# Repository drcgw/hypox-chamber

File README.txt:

Initial Raspberry Pi 4 set up

Using the Raspberry Pi OS installer (https://www.raspberrypi.com/software/) and a blank microSD card (128 GB Recommended) write the raspbian OS onto the SD card. Under the "operating system" menu select "Raspberry Pi OS (other)" and select "Raspberry Pi OS Full (32-bit)". Once the operating system is written to the SD card placed into Raspberry Pi. 

Once initial setup is completed go to terminal (Ctrl + T) and run the following codes:
    sudo apt update
    sudo apt full-upgrade

Next step is to download WiringPi:
    sudo apt-get update
    git clone https://github.com/WiringPi/WiringPi
    cd WiringPi
    ./build

Once these applications have been downloaded check the version by running:
    gpio -v
    gpio readall

System settings also need to be modified. Go to the configuration settings by using the following code: 
    sudo raspi-config
    
Under "Interfacing Options" insure that camera, SSH, VNC, SPI, I2C, Serial, and Remote GPIO are all enabled
System will require a reboot following these changes. The final items that need to be installed are all the python packaged and adafruit system requirements for CircuitPython. Tutorials and information can be found on Adafruit's website (https://learn.adafruit.com/welcome-to-circuitpython).
    sudo pip3 install adafruit-circuitpython-ads1x15
    sudo pip3 install adafruit-circuitpython-bme280
    sudo pip3 install adafruit-circuitpython-mcp9808
    sudo pip3 install adafruit-circuitpython-ccs811
    sudo pip3 install adafruit-circuitpython-bh1750

Once all the background files have been downloaded the github library can be downloaded using 
    wget https://github.com/drcgw/hypox-chamber.git

Unpack the files by unzipping and move RunChamber.sh file to the desktop.

Files can also be run manually through the terminal. Move the "PythonScript/" folder under "Documents/". If running manually before each run create a folder under "Documents/" with the following naming format "YYYY-MM-DD-Exposure/". Once inside this directory create: "FinalData/", "RawData/", "Calibration/" & "ImageCapture/" folders. After these folders have been created the exposure code can be run using the follow codes in the terminal. 
	cd Documents/PythonCodes/
	python3 2022-02-15-HC2000.py

If running it manually make sure that the most recent code has been installed and change the name in the second line of the above code to match the most recent copy of the .py script under the PythonCodes folder.

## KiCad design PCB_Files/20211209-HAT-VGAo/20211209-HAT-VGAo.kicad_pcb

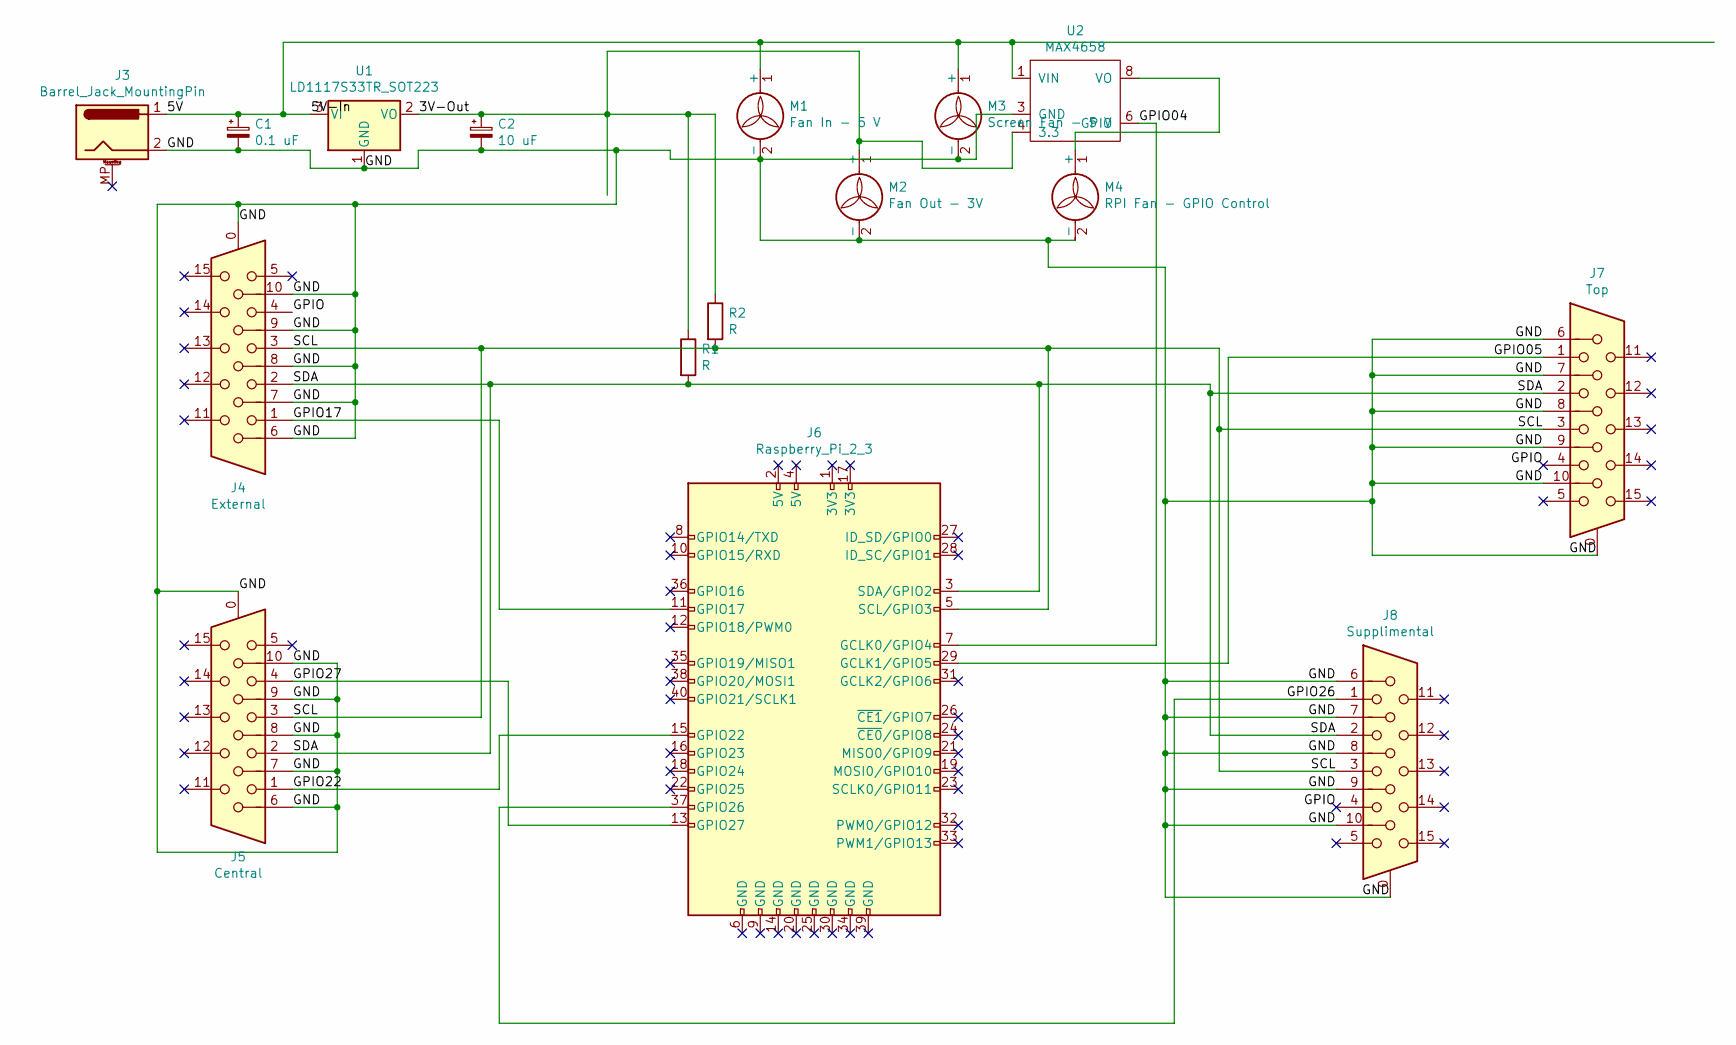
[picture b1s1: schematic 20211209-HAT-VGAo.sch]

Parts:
C1: 0.1 uF; C_Disc_D3.0mm_W2.0mm_P2.50mm
C2: 10 uF; CP_Radial_D5.0mm_P2.50mm
J3: Barrel_Jack_MountingPin; BarrelJack_Horizontal_w_MP
J4: External; DSUB-15-HD-Female-Horixonal_P2.29x2.54mm_EdgePinOffset8.35m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
J5: Central; DSUB-15-HD-Female-Horixonal_P2.29x2.54mm_EdgePinOffset8.35m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
J6: Raspberry_Pi_2_3; Raspberry_Pi_GPIO_ScrewAttachment
J7: Top; DSUB-15-HD-Female-Horixonal_P2.29x2.54mm_EdgePinOffset8.35m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
J8: Supplimental; DSUB-15-HD-Female-Horixonal_P2.29x2.54mm_EdgePinOffset8.35m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
M1: Fan In - 5 V; PinHeader_1x02_P2.54mm_Vertical (2)
M2: Fan Out - 3V; PinHeader_1x02_P2.54mm_Vertical (2)
M3: Screen Fan - 5 V; PinHeader_1x02_P2.54mm_Vertical (2)
M4: RPI Fan - GPIO Control; RPi_Fan_30mm_24mm
R1, R2: R; R_Axial_DIN0204_L3.6mm_D1.6mm_P7.62mm_Horizontal
U1: LD1117S33TR_SOT223; 3.3V_Regulator
U2: MAX4658

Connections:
/3V-Out: C2.1, M2.1 (+), R1.1, R2.1, U1.2 (VO), U2.4 (3.3)
/5V: C1.1, J3.1, M1.1 (+), M3.1 (+), U1.3 (VI), U2.1 (VIN)
/GND: C1.2, C2.2, J3.2, J4.0, J4.6, J4.7, J4.8, J4.9, J4.10, J5.0, J5.6, J5.7, J5.8, J5.9, J5.10, J7.0, J7.6, J7.7, J7.8, J7.9, J7.10, J8.0, J8.6, J8.7, J8.8, J8.9, J8.10, M1.2 (-), M2.2 (-), M3.2 (-), M4.2 (-), U1.1 (GND), U2.3 (GND)
/GPIO: J4.4, J7.4, J8.4
/GPIO04: J6.7 (GCLK0/GPIO4), U2.6 (GPIO)
/GPIO05: J6.29 (GCLK1/GPIO5), J7.1
/GPIO17: J4.1, J6.11 (GPIO17)
/GPIO22: J5.1, J6.15 (GPIO22)
/GPIO26: J6.37 (GPIO26), J8.1
/GPIO27: J5.4, J6.13 (GPIO27)
/SCL: J4.3, J5.3, J6.5 (SCL/GPIO3), J7.3, J8.3, R2.2
/SDA: J4.2, J5.2, J6.3 (SDA/GPIO2), J7.2, J8.2, R1.2
unnamed: M4.1 (+), U2.8 (VO)

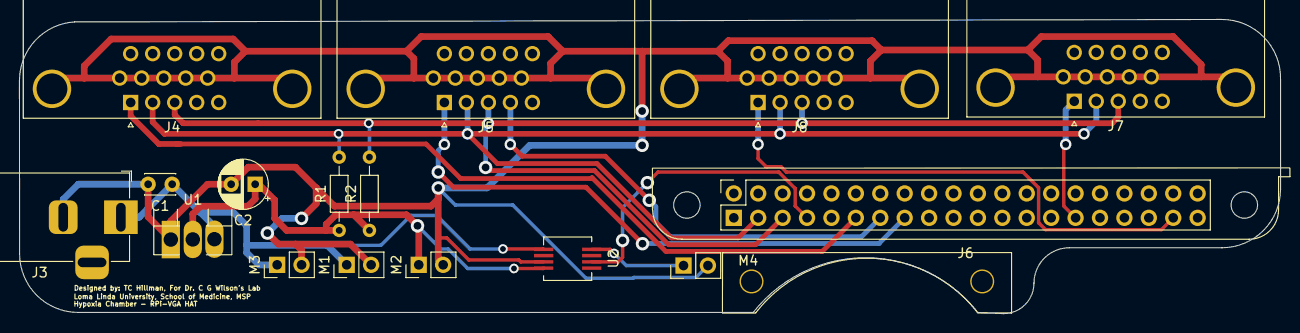
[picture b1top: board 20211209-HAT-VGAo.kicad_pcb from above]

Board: 2 copper layers, 131.2 x 30.6 mm, 16 parts (0 on the bottom side), 13 nets.

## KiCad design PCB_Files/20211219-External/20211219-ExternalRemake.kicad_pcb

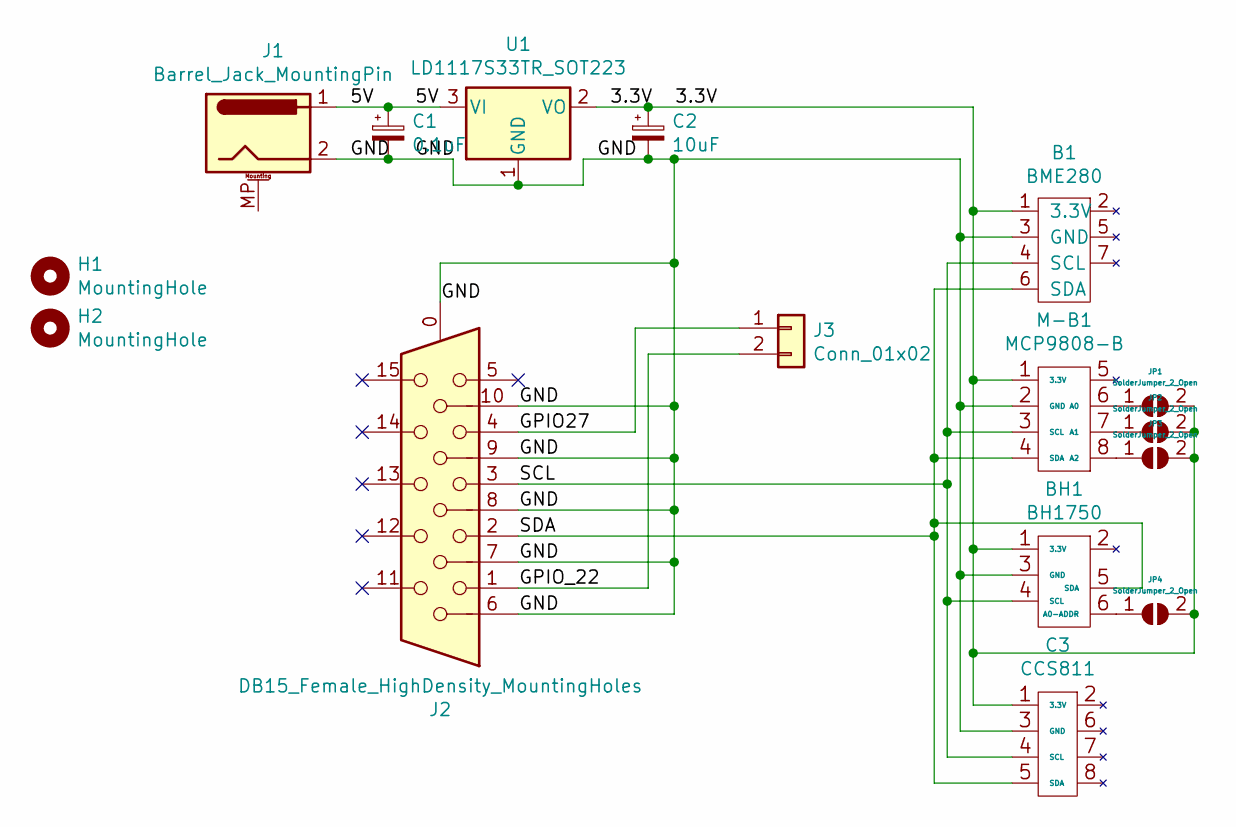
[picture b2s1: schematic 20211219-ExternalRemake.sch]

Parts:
B1: BME280; PinHeader_1x07_P2.54mm_Vertical
BH1: BH1750; PinHeader_1x06_P2.54mm_Vertical
C1: 0.1uF; C_Disc_D5.1mm_W3.2mm_P5.00mm
C2: 10uF; CP_Radial_D6.3mm_P2.50mm
C3: CCS811; PinHeader_1x08_P2.54mm_Vertical
H1, H2: MountingHole; MountingHole_2.7mm_M2.5_DIN965_Pad_TopBottom
J1: Barrel_Jack_MountingPin; BarrelJack_Horizontal_w_MP
J2: DB15_Female_HighDensity_MountingHoles; DSUB-15-HD-Female-Horixonal_P2.29x2.54mm_EdgePinOffset8.35m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
J3: Conn_01x02; PinHeader_1x02_P2.54mm_Vertical
JP1, JP2, JP3, JP4: SolderJumper_2_Open; SolderJumper-2_P1.3mm_Open_TrianglePad1.0x1.5mm
M-B1: MCP9808-B; PinHeader_1x08_P2.54mm_Vertical
U1: LD1117S33TR_SOT223; 3.3V_Regulator

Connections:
/3.3V: B1.1 (3.3V), BH1.1 (3.3V), C2.1, C3.1 (3.3V), JP1.2 (B), JP2.2 (B), JP3.2 (B), JP4.2 (B), M-B1.1 (3.3V), U1.2 (VO)
/5V: C1.1, J1.1, U1.3 (VI)
/GND: B1.3 (GND), BH1.3 (GND), C1.2, C2.2, C3.3 (GND), J1.2, J2.0, J2.6, J2.7, J2.8, J2.9, J2.10, M-B1.2 (GND), U1.1 (GND)
/GPIO27: J2.4, J3.1
/GPIO_22: J2.1, J3.2
/SCL: B1.4 (SCL), BH1.4 (SCL), C3.4 (SCL), J2.3, M-B1.3 (SCL)
/SDA: B1.6 (SDA), BH1.5 (SDA), C3.5 (SDA), J2.2, M-B1.4 (SDA)
unnamed: BH1.6 (A0-ADDR), JP4.1 (A)
unnamed: JP1.1 (A), M-B1.6 (A0)
unnamed: JP2.1 (A), M-B1.7 (A1)
unnamed: JP3.1 (A), M-B1.8 (A2)

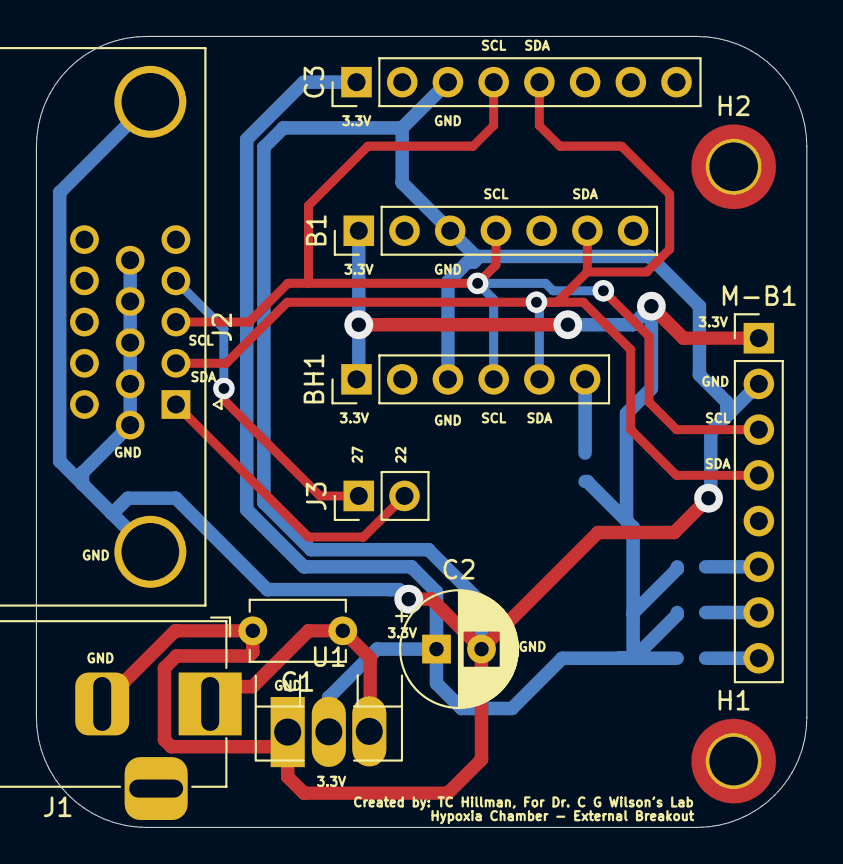
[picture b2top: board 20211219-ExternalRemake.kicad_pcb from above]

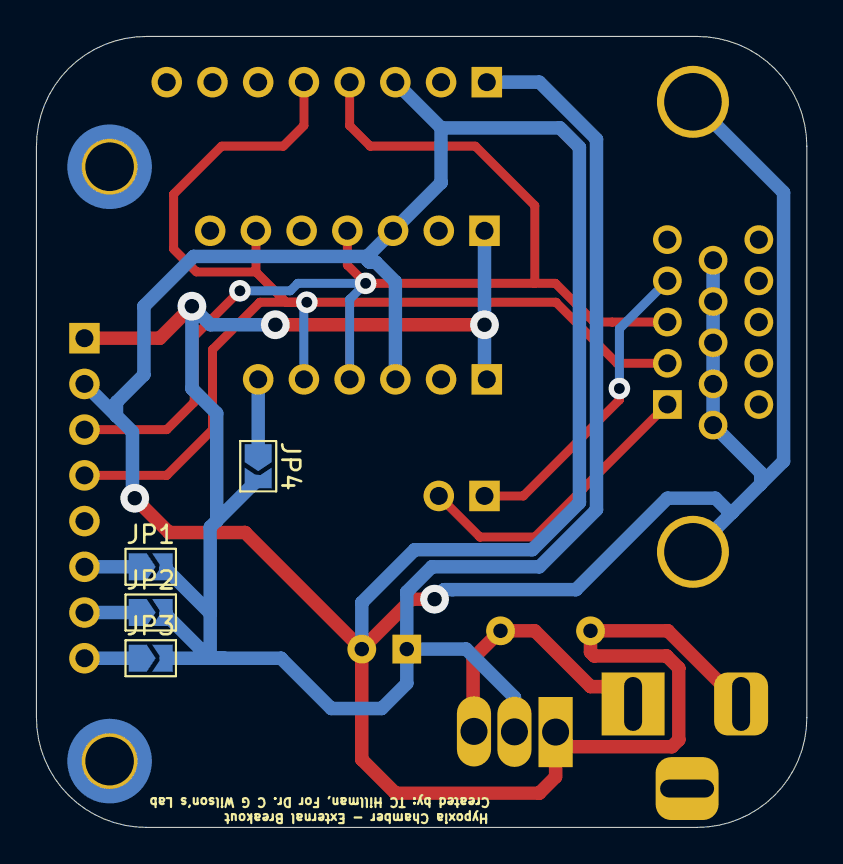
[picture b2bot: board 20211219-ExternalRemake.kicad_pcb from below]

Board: 2 copper layers, 42.8 x 43.9 mm, 16 parts (4 on the bottom side), 11 nets.

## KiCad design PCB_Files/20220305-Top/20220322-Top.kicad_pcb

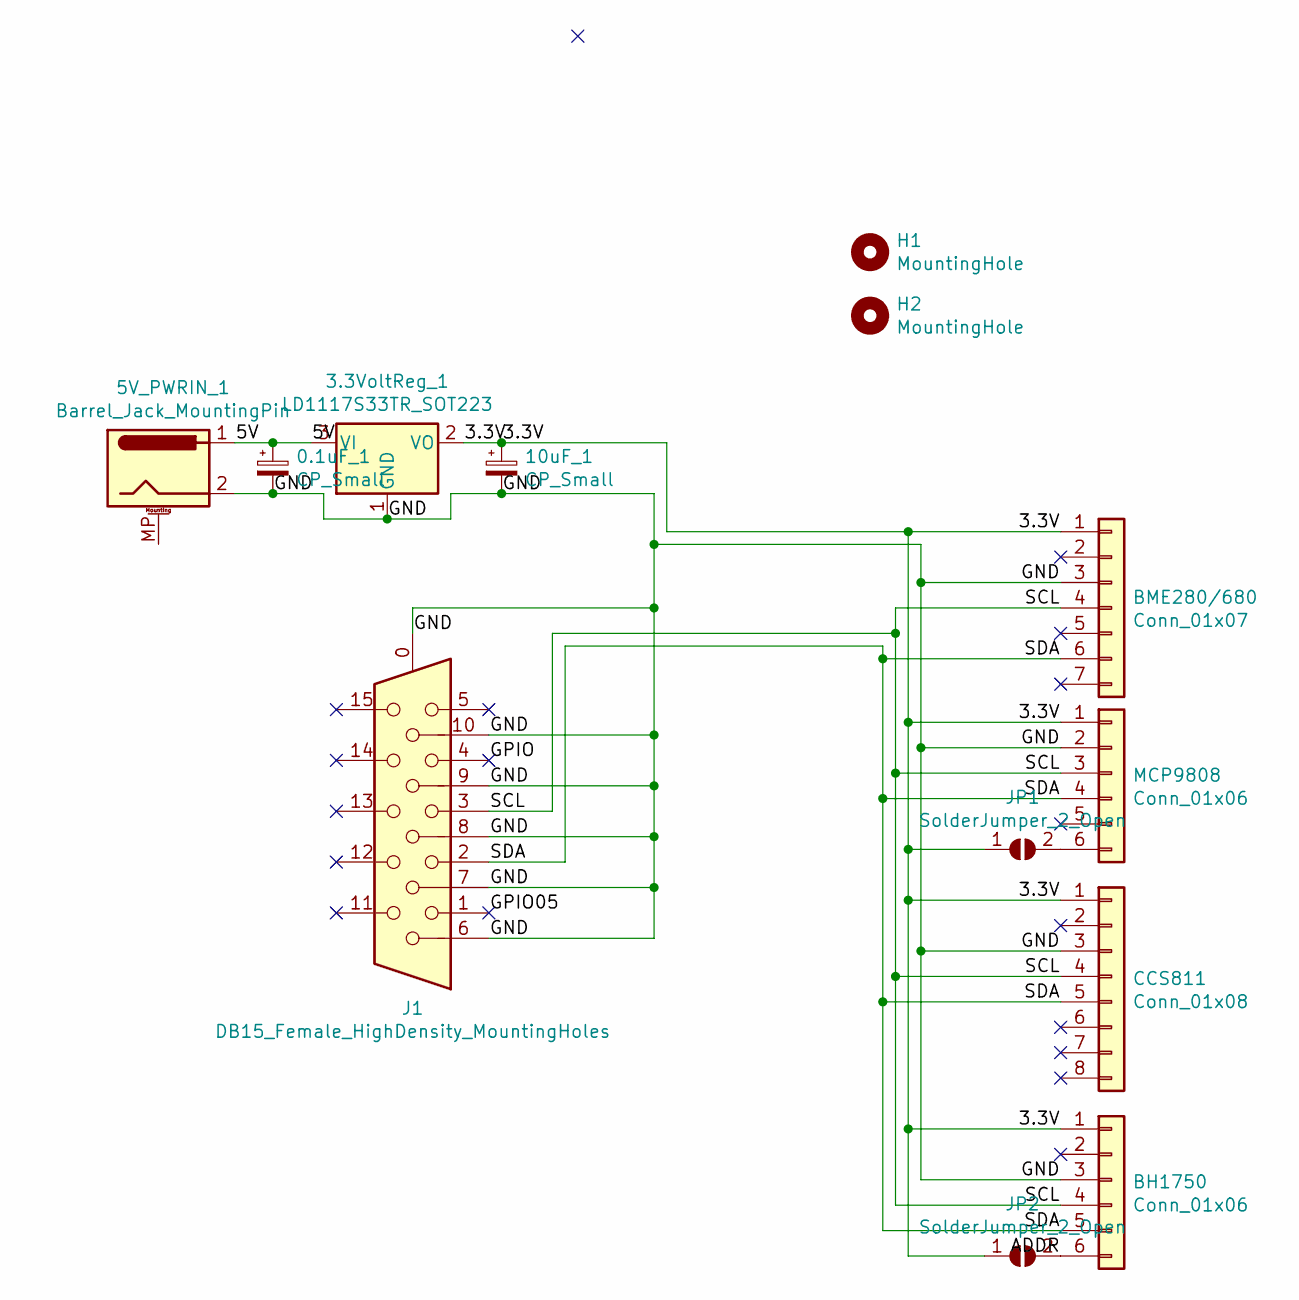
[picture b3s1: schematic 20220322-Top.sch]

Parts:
0.1uF_1: CP_Small; C_Disc_0.1uF_D3.8mm_W2.6mm_P2.50mm
3.3VoltReg_1: LD1117S33TR_SOT223; 3.3V_Regulator
5V_PWRIN_1: Barrel_Jack_MountingPin; BarrelJack_Horizontal_w_MP
10uF_1: CP_Small; CP_10uF_Radial_D6.3mm_P2.50mm
BH1750: Conn_01x06; PinHeader_1x06_P2.54mm_Vertical
BME280/680: Conn_01x07; PinHeader_1x07_P2.54mm_Vertical
CCS811: Conn_01x08; PinHeader_1x08_P2.54mm_Vertical
H1, H2: MountingHole; MountingHole_2.5mm_Pad_TopBottom
J1: DB15_Female_HighDensity_MountingHoles; DSUB-15-HD-Female-Horixonal_P2.29x2.54mm_EdgePinOffset8.35m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
JP1, JP2: SolderJumper_2_Open; SolderJumper-2_P1.3mm_Open_TrianglePad1.0x1.5mm
MCP9808: Conn_01x06; PinHeader_1x06_P2.54mm_Vertical

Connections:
/3.3V: 3.3VoltReg_1.2 (VO), 10uF_1.1, BH1750.1, BME280/680.1, CCS811.1, JP1.1 (A), JP2.1 (A), MCP9808.1
/5V: 0.1uF_1.1, 3.3VoltReg_1.3 (VI), 5V_PWRIN_1.1
/ADDR: BH1750.6, JP2.2 (B)
/GND: 0.1uF_1.2, 3.3VoltReg_1.1 (GND), 5V_PWRIN_1.2, 10uF_1.2, BH1750.3, BME280/680.3, CCS811.3, J1.0, J1.6, J1.7, J1.8, J1.9, J1.10, MCP9808.2
/GPIO: J1.4
/GPIO05: J1.1
/SCL: BH1750.4, BME280/680.4, CCS811.4, J1.3, MCP9808.3
/SDA: BH1750.5, BME280/680.6, CCS811.5, J1.2, MCP9808.4
unnamed: JP1.2 (B), MCP9808.6

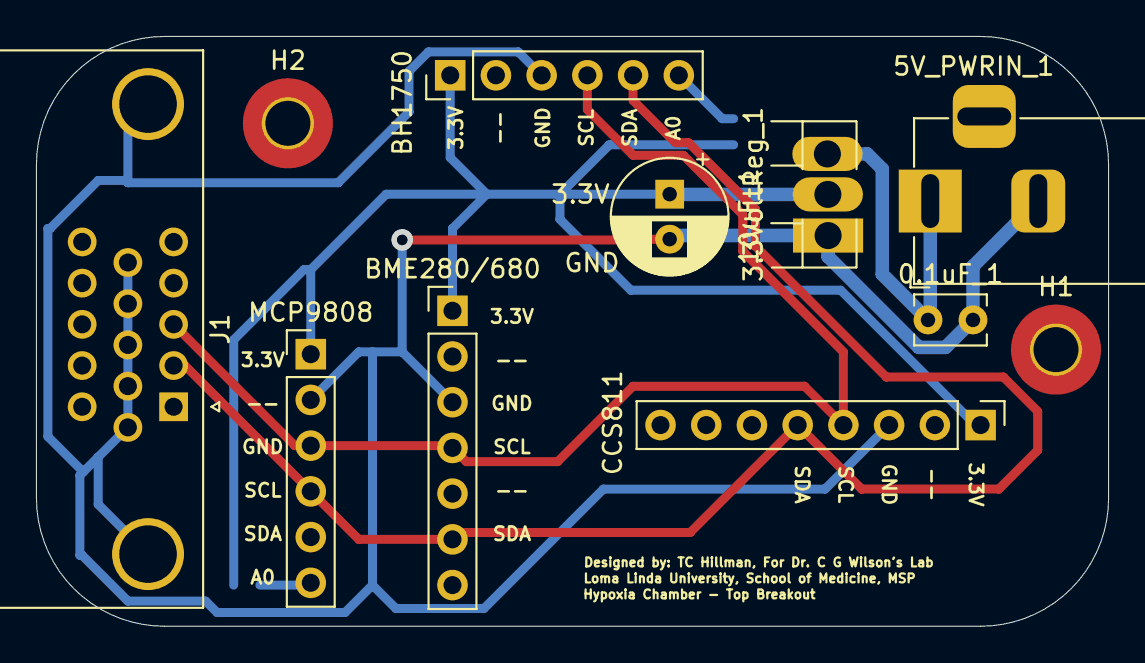
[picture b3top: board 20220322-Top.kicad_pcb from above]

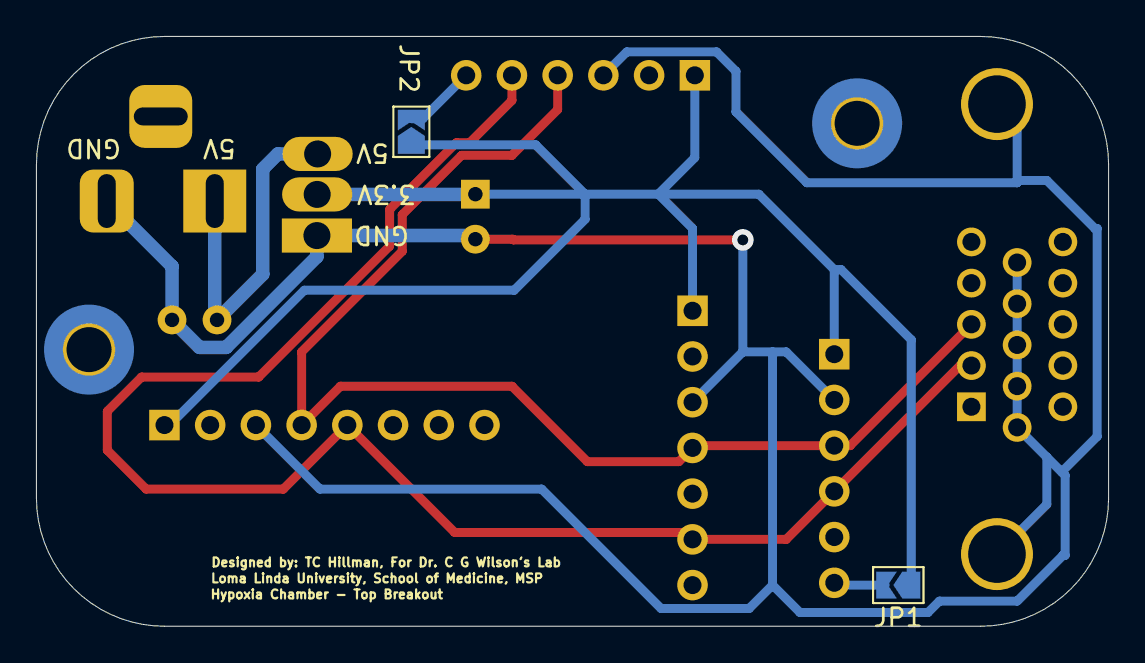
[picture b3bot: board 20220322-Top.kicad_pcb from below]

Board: 2 copper layers, 59.6 x 32.8 mm, 13 parts (2 on the bottom side), 7 nets.

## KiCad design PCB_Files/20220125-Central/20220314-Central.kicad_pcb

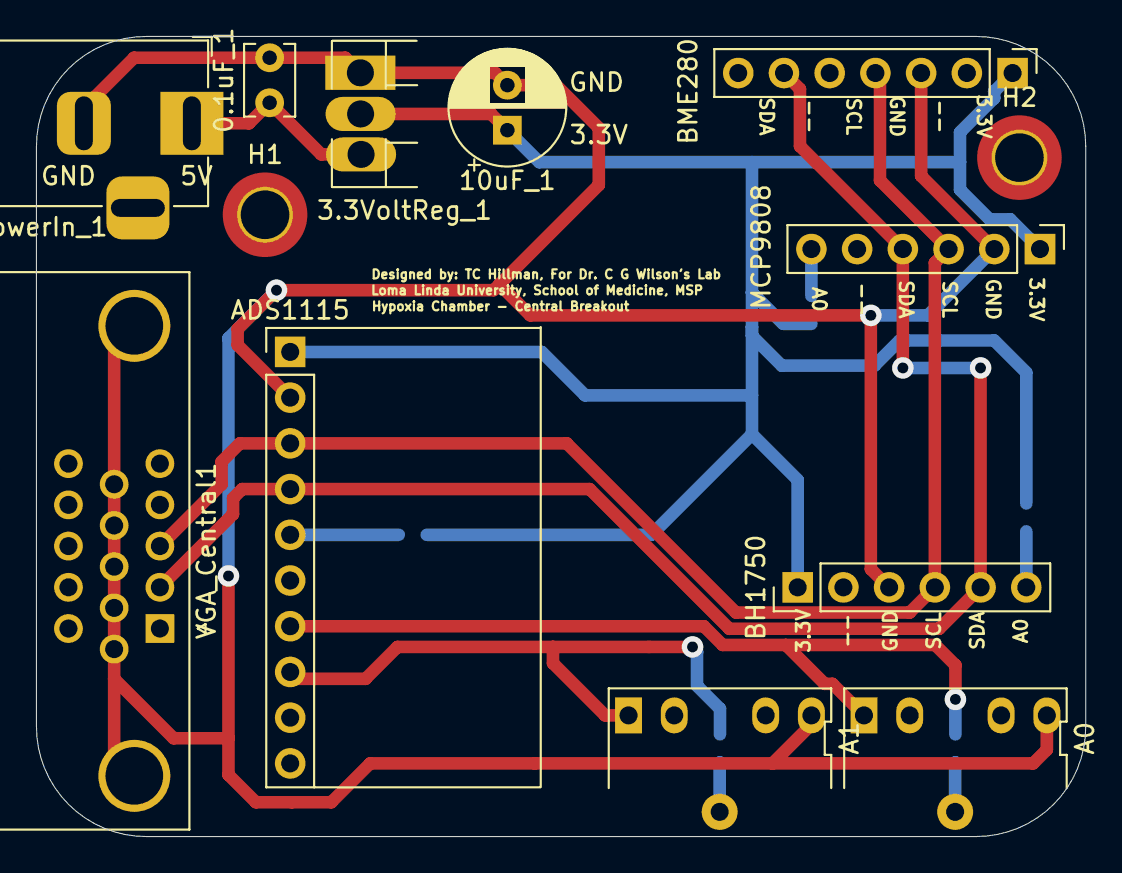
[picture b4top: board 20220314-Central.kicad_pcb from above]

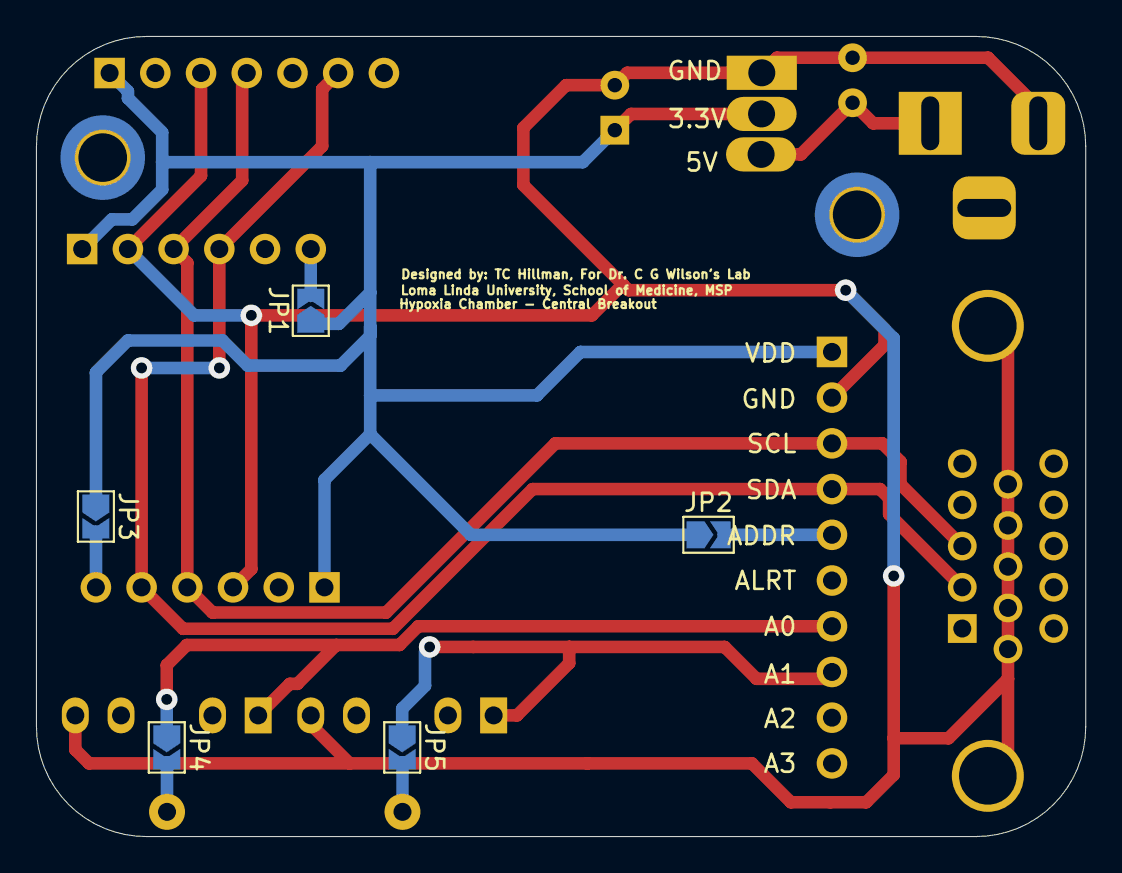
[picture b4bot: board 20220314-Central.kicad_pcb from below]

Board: 2 copper layers, 58.3 x 44.5 mm, 18 parts (5 on the bottom side), 11 nets.

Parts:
0.1uF_1: CP_Small; C_Disc_0.1uF_D3.8mm_W2.6mm_P2.50mm
3.3VoltReg_1: LD1117S33TR_SOT223; 3.3V_Regulator
10uF_1: CP_Small; CP_10uF_Radial_D6.3mm_P2.50mm
A0, A1: AudioJack3; 20220314-UniversalAux
ADS1115: Conn_01x10; ADS1115
BH1750: Conn_01x06; PinHeader_1x06_P2.54mm_Vertical
BME280: Conn_01x07; PinHeader_1x07_P2.54mm_Vertical
H1, H2: MountingHole; MountingHole_2.7mm_M2.5_DIN965_Pad_TopBottom
JP1, JP2, JP3, JP4, JP5: SolderJumper_2_Open; SolderJumper-2_P1.3mm_Open_TrianglePad1.0x1.5mm
MCP9808: Conn_01x06; PinHeader_1x06_P2.54mm_Vertical
PowerIn_1: Barrel_Jack_MountingPin; BarrelJack_Horizontal_w_MP
VGA_Central1: DB15_Female_HighDensity_MountingHoles; DSUB-15-HD-Female-Horixonal_P2.29x2.54mm_EdgePinOffset8.35m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

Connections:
/3.3VIn: 3.3VoltReg_1.2, 10uF_1.1, ADS1115.1, BH1750.1, BME280.1, JP1.1, JP2.1, JP3.1, MCP9808.1
/5v: 0.1uF_1.1, 3.3VoltReg_1.3, PowerIn_1.1
/A0: A0.S, ADS1115.7, JP4.1
/A1: A1.S, ADS1115.8, JP5.1
/ADDR: ADS1115.5, BH1750.6, JP2.2, JP3.2
/Ad0: JP1.2, MCP9808.6
/GND: 0.1uF_1.2, 3.3VoltReg_1.1, 10uF_1.2, A0.T, A1.T, ADS1115.2, BH1750.3, BME280.3, MCP9808.2, PowerIn_1.2, VGA_Central1.0, VGA_Central1.6, VGA_Central1.7, VGA_Central1.8, VGA_Central1.9, VGA_Central1.10
/SCL: ADS1115.3, BH1750.4, BME280.4, MCP9808.3, VGA_Central1.3
/SDA: ADS1115.4, BH1750.5, BME280.6, MCP9808.4, VGA_Central1.2
unnamed: A0.R, JP4.2
unnamed: A1.R, JP5.2

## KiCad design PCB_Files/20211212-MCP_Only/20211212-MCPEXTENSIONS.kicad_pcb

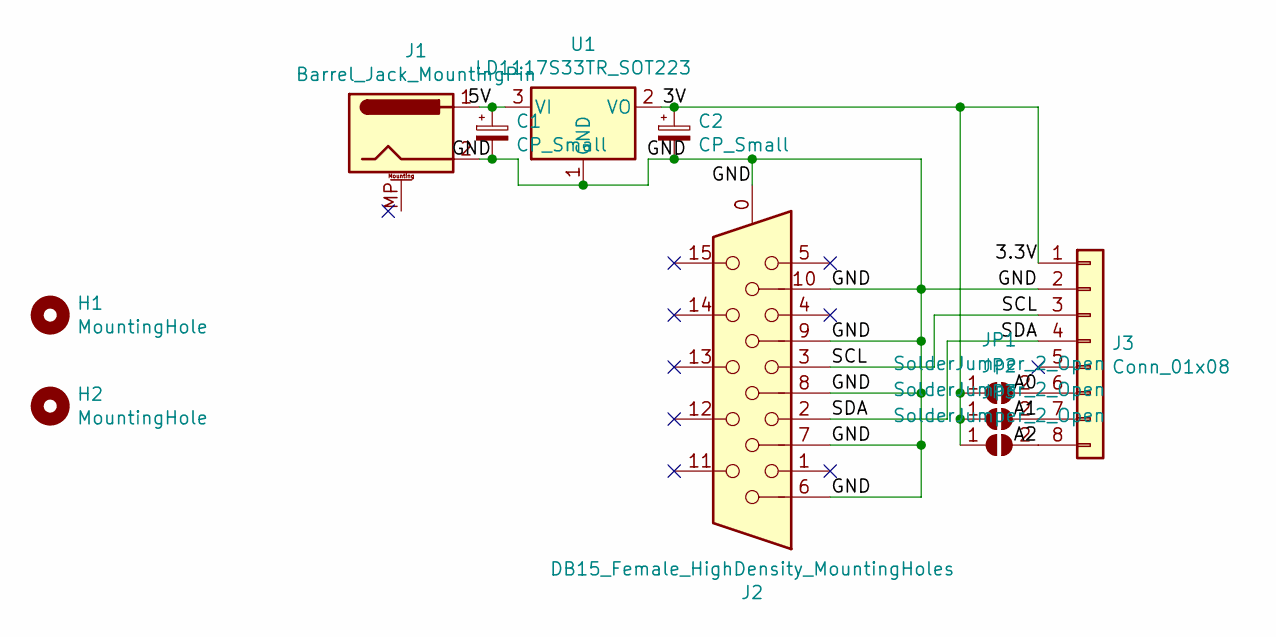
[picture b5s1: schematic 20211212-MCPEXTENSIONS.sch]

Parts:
C1: CP_Small; C_Disc_0.1uF_D3.8mm_W2.6mm_P2.50mm
C2: CP_Small; CP_10uF_Radial_D6.3mm_P2.50mm
H1, H2: MountingHole; MountingHole_2.5mm_Pad_TopBottom
J1: Barrel_Jack_MountingPin; BarrelJack_Horizontal_w_MP
J2: DB15_Female_HighDensity_MountingHoles; DSUB-15-HD-Female-Horixonal_P2.29x2.54mm_EdgePinOffset8.35m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
J3: Conn_01x08; PinHeader_1x08_P2.54mm_Vertical
JP1, JP2, JP3: SolderJumper_2_Open; SolderJumper-2_P1.3mm_Open_TrianglePad1.0x1.5mm (2)
U1: LD1117S33TR_SOT223; 3.3V_Regulator

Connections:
/3.3V: C2.1, J3.1, JP1.1 (A), JP2.1 (A), JP3.1 (A), U1.2 (VO)
/5V: C1.1, J1.1, U1.3 (VI)
/A0: J3.6, JP1.2 (B)
/A1: J3.7, JP2.2 (B)
/A2: J3.8, JP3.2 (B)
/GND: C1.2, C2.2, J1.2, J2.0, J2.6, J2.7, J2.8, J2.9, J2.10, J3.2, U1.1 (GND)
/SCL: J2.3, J3.3
/SDA: J2.2, J3.4

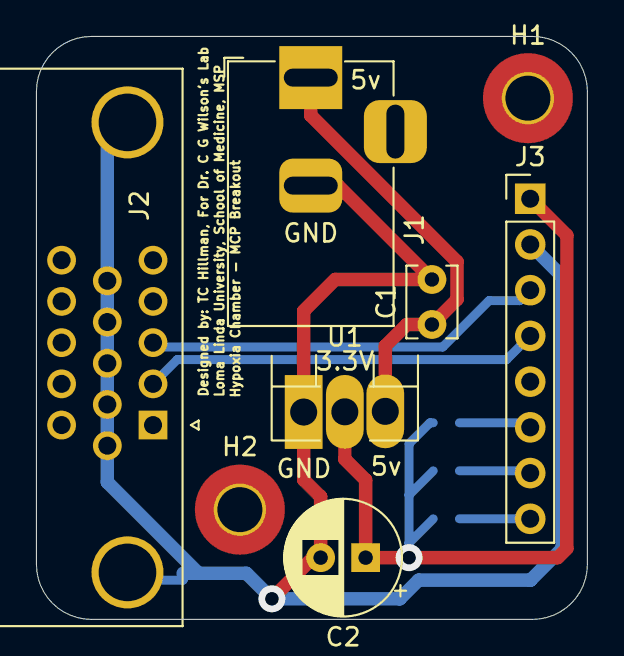
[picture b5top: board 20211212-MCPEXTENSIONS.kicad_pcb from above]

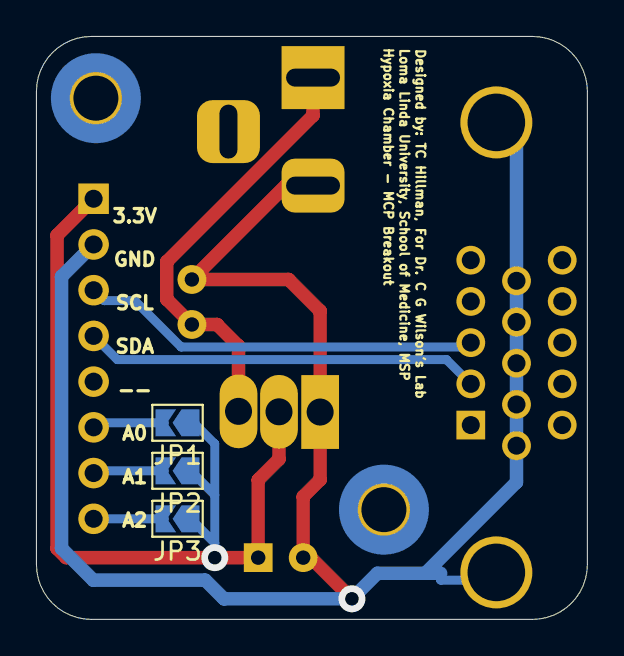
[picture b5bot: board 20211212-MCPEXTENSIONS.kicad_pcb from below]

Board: 2 copper layers, 30.6 x 32.4 mm, 11 parts (3 on the bottom side), 8 nets.

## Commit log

2022-02-22 Initial addition of files and folder for data collection. Files getting prepared for push to github repository https://github.com/drcgw/hypox-chamber.git.
2022-02-23 Addition of 3D design files to git hub library, currently only the Raspberry Pi holder is included in these files. Additional flies for board mounting is still in design.
2022-02-23 Updated README file
2022-06-03 Set theme jekyll-theme-modernist
2022-06-04 Started introduction and page name
2022-06-05 Updated_Index
2022-06-05 Overview Image
2022-06-05 Basic Introduction page
2022-06-05 Basic User Webpage
